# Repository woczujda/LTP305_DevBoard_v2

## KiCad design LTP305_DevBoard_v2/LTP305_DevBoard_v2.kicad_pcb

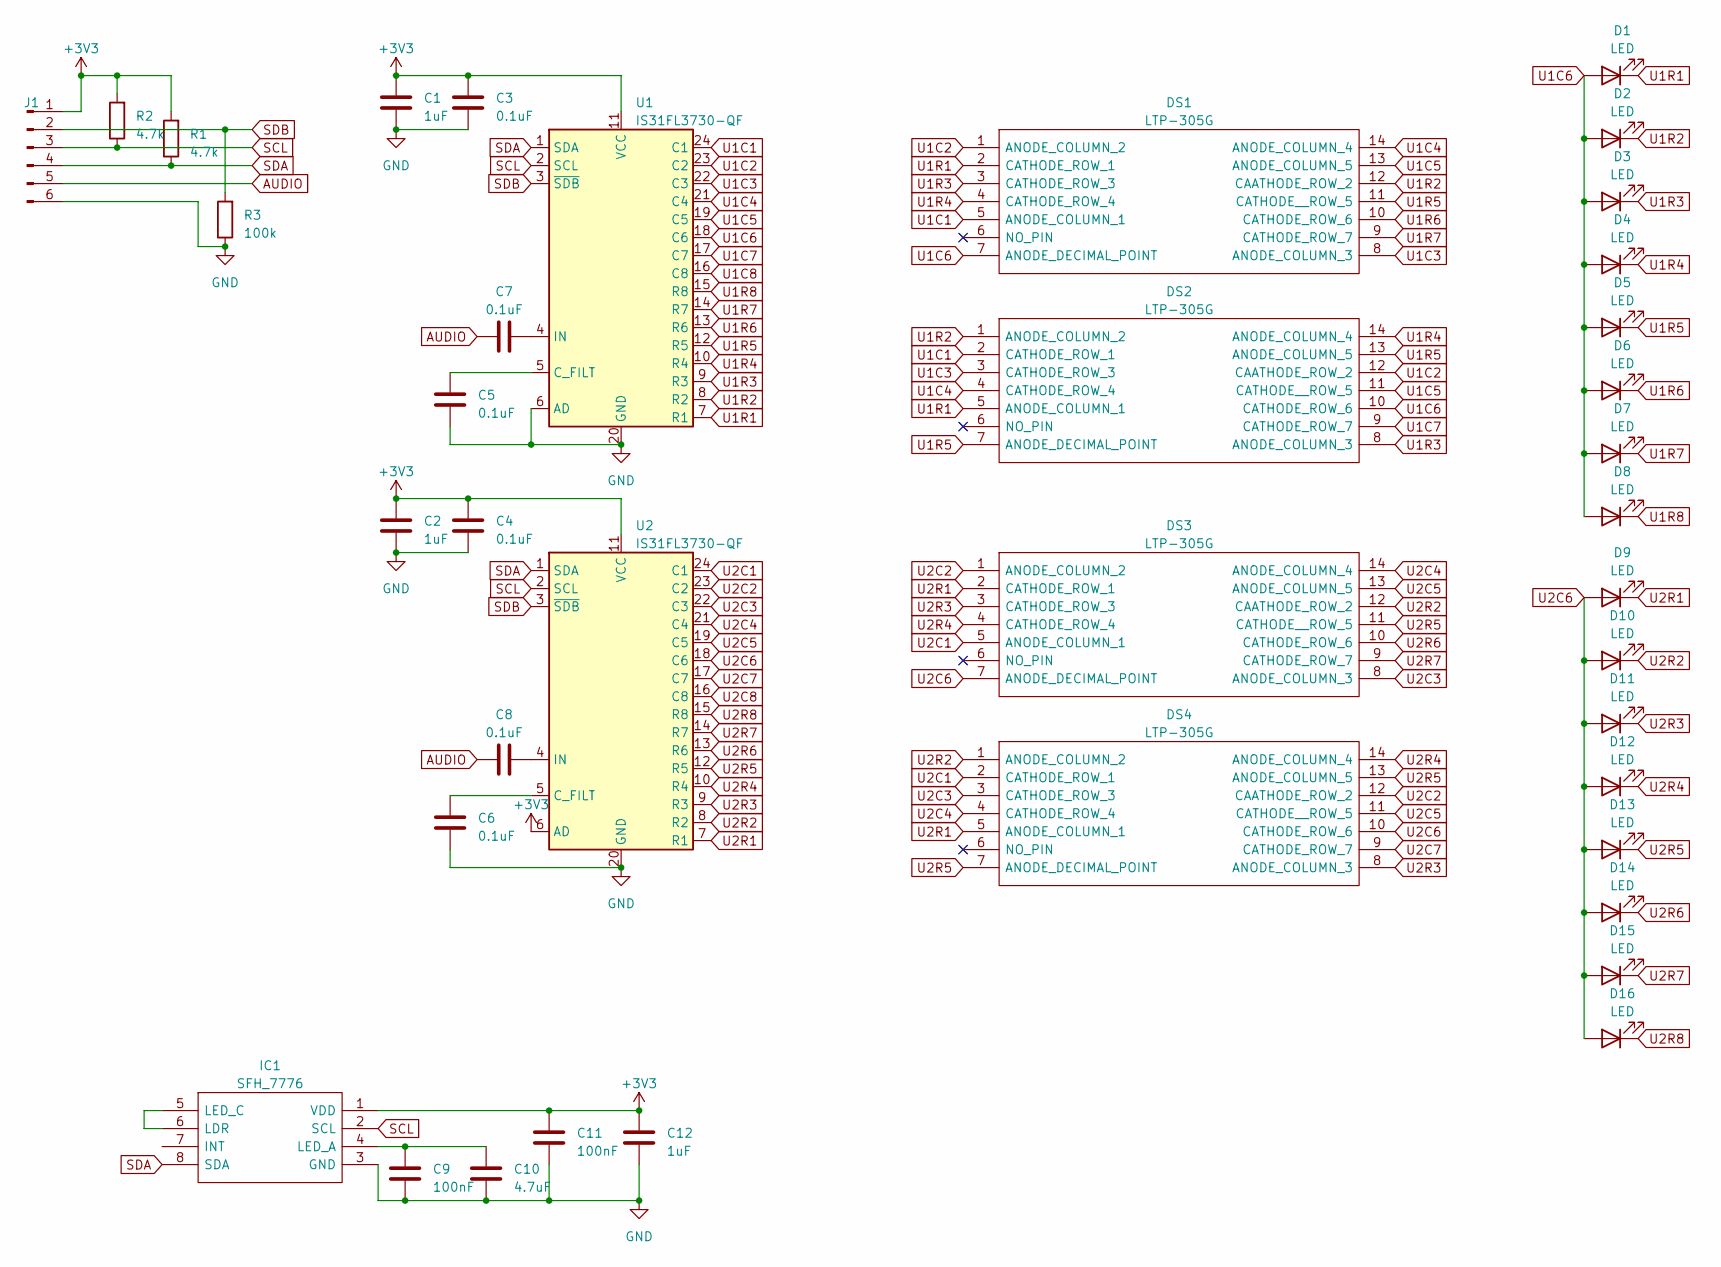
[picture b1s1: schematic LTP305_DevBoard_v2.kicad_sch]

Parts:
C1, C2, C12: 1uF; C_0603_1608Metric
C3, C4, C5, C6, C7, C8: 0.1uF; C_0603_1608Metric
C9, C11: 100nF; C_0603_1608Metric
C10: 4.7uF; C_0603_1608Metric
D1, D2, D3, D4, D5, D6, D7, D8, D9, D10, D11, D12, D13, D14, D15, D16: LED; LED_0603_1608Metric
DS1, DS2, DS3, DS4: LTP-305G; DIPS762W50P254L1850H400Q14N; Mouser Part Number 859-LTP-305G
IC1: SFH_7776; SFH7776; Mouser Part Number 720-SFH7776
J1: Conn_01x07_Pin; PinHeader_1x06_P2.54mm_Vertical
R1, R2: 4.7k; R_0603_1608Metric
R3: 100k; R_0603_1608Metric
U1, U2: IS31FL3730-QF; QFN-28-1EP_4x4mm_P0.4mm_EP2.3x2.3mm

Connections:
+3V3: C1.2, C2.2, C3.2, C4.2, C11.2, C12.2, IC1.1 (VDD), J1.1, R1.2, R2.2, U1.11 (VCC), U2.6 (AD), U2.11 (VCC)
AUDIO: C7.1, C8.1, J1.5
GND: C1.1, C2.1, C3.1, C4.1, C5.1, C6.1, C9.1, C10.1, C11.1, C12.1, IC1.3 (GND), J1.6, R3.1, U1.6 (AD), U1.20 (GND), U2.20 (GND), U2.29
unnamed: IC1.5 (LED_C), IC1.6 (LDR)
unnamed: C9.2, C10.2, IC1.4 (LED_A)
unnamed: C5.2, U1.5 (C_FILT)
unnamed: C7.2, U1.4 (IN)
unnamed: C6.2, U2.5 (C_FILT)
unnamed: C8.2, U2.4 (IN)
SCL: IC1.2 (SCL), J1.3, R2.1, U1.2 (SCL), U2.2 (SCL)
SDA: IC1.8 (SDA), J1.4, R1.1, U1.1 (SDA), U2.1 (SDA)
SDB: J1.2, R3.2, U1.3 (~SDB), U2.3 (~SDB)
U1C1: DS1.5 (ANODE_COLUMN_1), DS2.2 (CATHODE_ROW_1), U1.24 (C1)
U1C2: DS1.1 (ANODE_COLUMN_2), DS2.12 (CAATHODE_ROW_2), U1.23 (C2)
U1C3: DS1.8 (ANODE_COLUMN_3), DS2.3 (CATHODE_ROW_3), U1.22 (C3)
U1C4: DS1.14 (ANODE_COLUMN_4), DS2.4 (CATHODE_ROW_4), U1.21 (C4)
U1C5: DS1.13 (ANODE_COLUMN_5), DS2.11 (CATHODE__ROW_5), U1.19 (C5)
U1C6: D1.2 (A), D2.2 (A), D3.2 (A), D4.2 (A), D5.2 (A), D6.2 (A), D7.2 (A), D8.2 (A), DS1.7 (ANODE_DECIMAL_POINT), DS2.10 (CATHODE_ROW_6), U1.18 (C6)
U1C7: DS2.9 (CATHODE_ROW_7), U1.17 (C7)
U1C8: U1.16 (C8)
U1R1: D1.1 (K), DS1.2 (CATHODE_ROW_1), DS2.5 (ANODE_COLUMN_1), U1.7 (R1)
U1R2: D2.1 (K), DS1.12 (CAATHODE_ROW_2), DS2.1 (ANODE_COLUMN_2), U1.8 (R2)
U1R3: D3.1 (K), DS1.3 (CATHODE_ROW_3), DS2.8 (ANODE_COLUMN_3), U1.9 (R3)
U1R4: D4.1 (K), DS1.4 (CATHODE_ROW_4), DS2.14 (ANODE_COLUMN_4), U1.10 (R4)
U1R5: D5.1 (K), DS1.11 (CATHODE__ROW_5), DS2.7 (ANODE_DECIMAL_POINT), DS2.13 (ANODE_COLUMN_5), U1.12 (R5)
U1R6: D6.1 (K), DS1.10 (CATHODE_ROW_6), U1.13 (R6)
U1R7: D7.1 (K), DS1.9 (CATHODE_ROW_7), U1.14 (R7)
U1R8: D8.1 (K), U1.15 (R8)
U2C1: DS3.5 (ANODE_COLUMN_1), DS4.2 (CATHODE_ROW_1), U2.24 (C1)
U2C2: DS3.1 (ANODE_COLUMN_2), DS4.12 (CAATHODE_ROW_2), U2.23 (C2)
U2C3: DS3.8 (ANODE_COLUMN_3), DS4.3 (CATHODE_ROW_3), U2.22 (C3)
U2C4: DS3.14 (ANODE_COLUMN_4), DS4.4 (CATHODE_ROW_4), U2.21 (C4)
U2C5: DS3.13 (ANODE_COLUMN_5), DS4.11 (CATHODE__ROW_5), U2.19 (C5)
U2C6: D9.2 (A), D10.2 (A), D11.2 (A), D12.2 (A), D13.2 (A), D14.2 (A), D15.2 (A), D16.2 (A), DS3.7 (ANODE_DECIMAL_POINT), DS4.10 (CATHODE_ROW_6), U2.18 (C6)
U2C7: DS4.9 (CATHODE_ROW_7), U2.17 (C7)
U2C8: U2.16 (C8)
U2R1: D9.1 (K), DS3.2 (CATHODE_ROW_1), DS4.5 (ANODE_COLUMN_1), U2.7 (R1)
U2R2: D10.1 (K), DS3.12 (CAATHODE_ROW_2), DS4.1 (ANODE_COLUMN_2), U2.8 (R2)
U2R3: D11.1 (K), DS3.3 (CATHODE_ROW_3), DS4.8 (ANODE_COLUMN_3), U2.9 (R3)
U2R4: D12.1 (K), DS3.4 (CATHODE_ROW_4), DS4.14 (ANODE_COLUMN_4), U2.10 (R4)
U2R5: D13.1 (K), DS3.11 (CATHODE__ROW_5), DS4.7 (ANODE_DECIMAL_POINT), DS4.13 (ANODE_COLUMN_5), U2.12 (R5)
U2R6: D14.1 (K), DS3.10 (CATHODE_ROW_6), U2.13 (R6)
U2R7: D15.1 (K), DS3.9 (CATHODE_ROW_7), U2.14 (R7)
U2R8: D16.1 (K), U2.15 (R8)

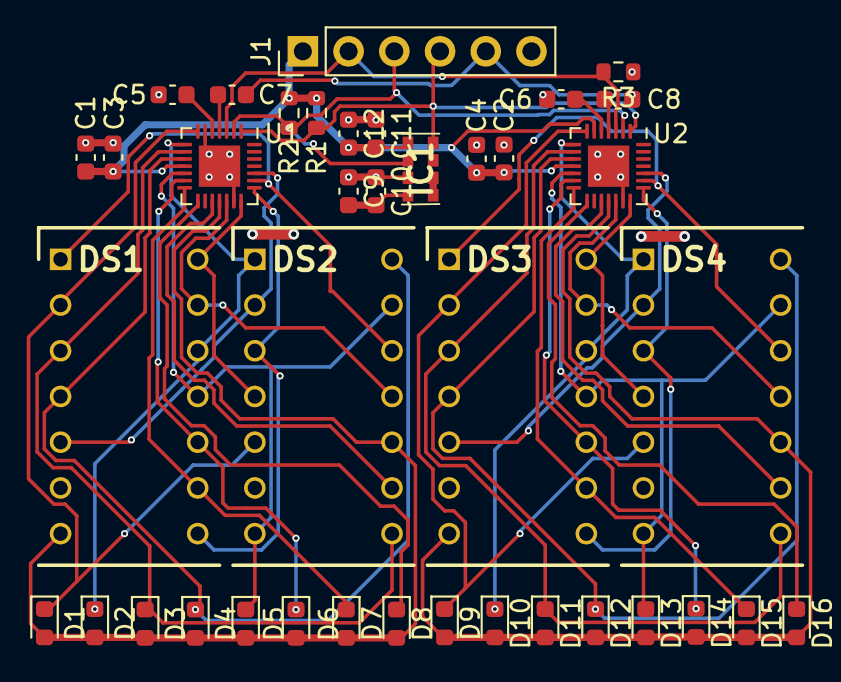
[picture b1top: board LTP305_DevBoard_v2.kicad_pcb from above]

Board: 2 copper layers, 39 parts (0 on the bottom side), 42 nets.

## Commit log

2023-03-25 Initial Design
